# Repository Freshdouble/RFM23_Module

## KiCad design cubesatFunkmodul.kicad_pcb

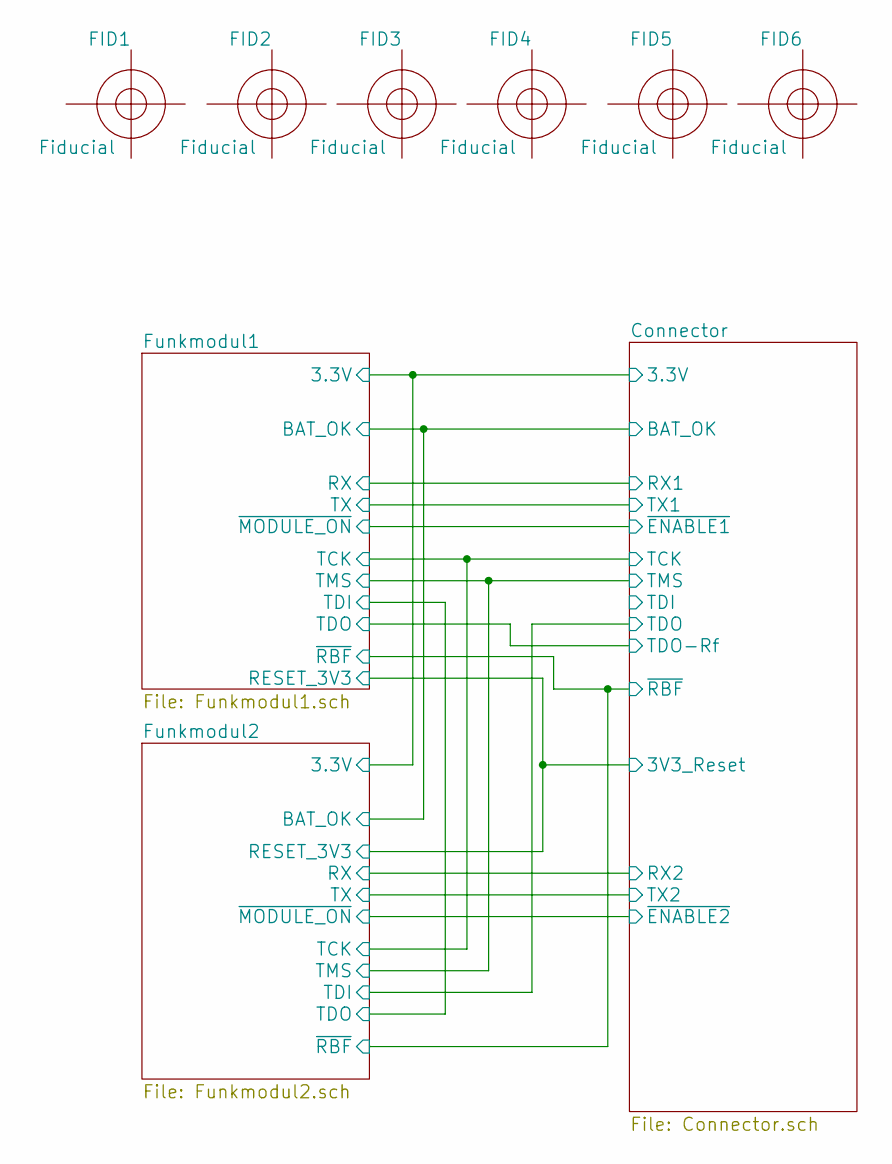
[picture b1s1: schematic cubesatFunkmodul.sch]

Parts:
FID1, FID2, FID3, FID4, FID5, FID6: Fiducial; Fiducial_0.5mm_Dia_1mm_Outer

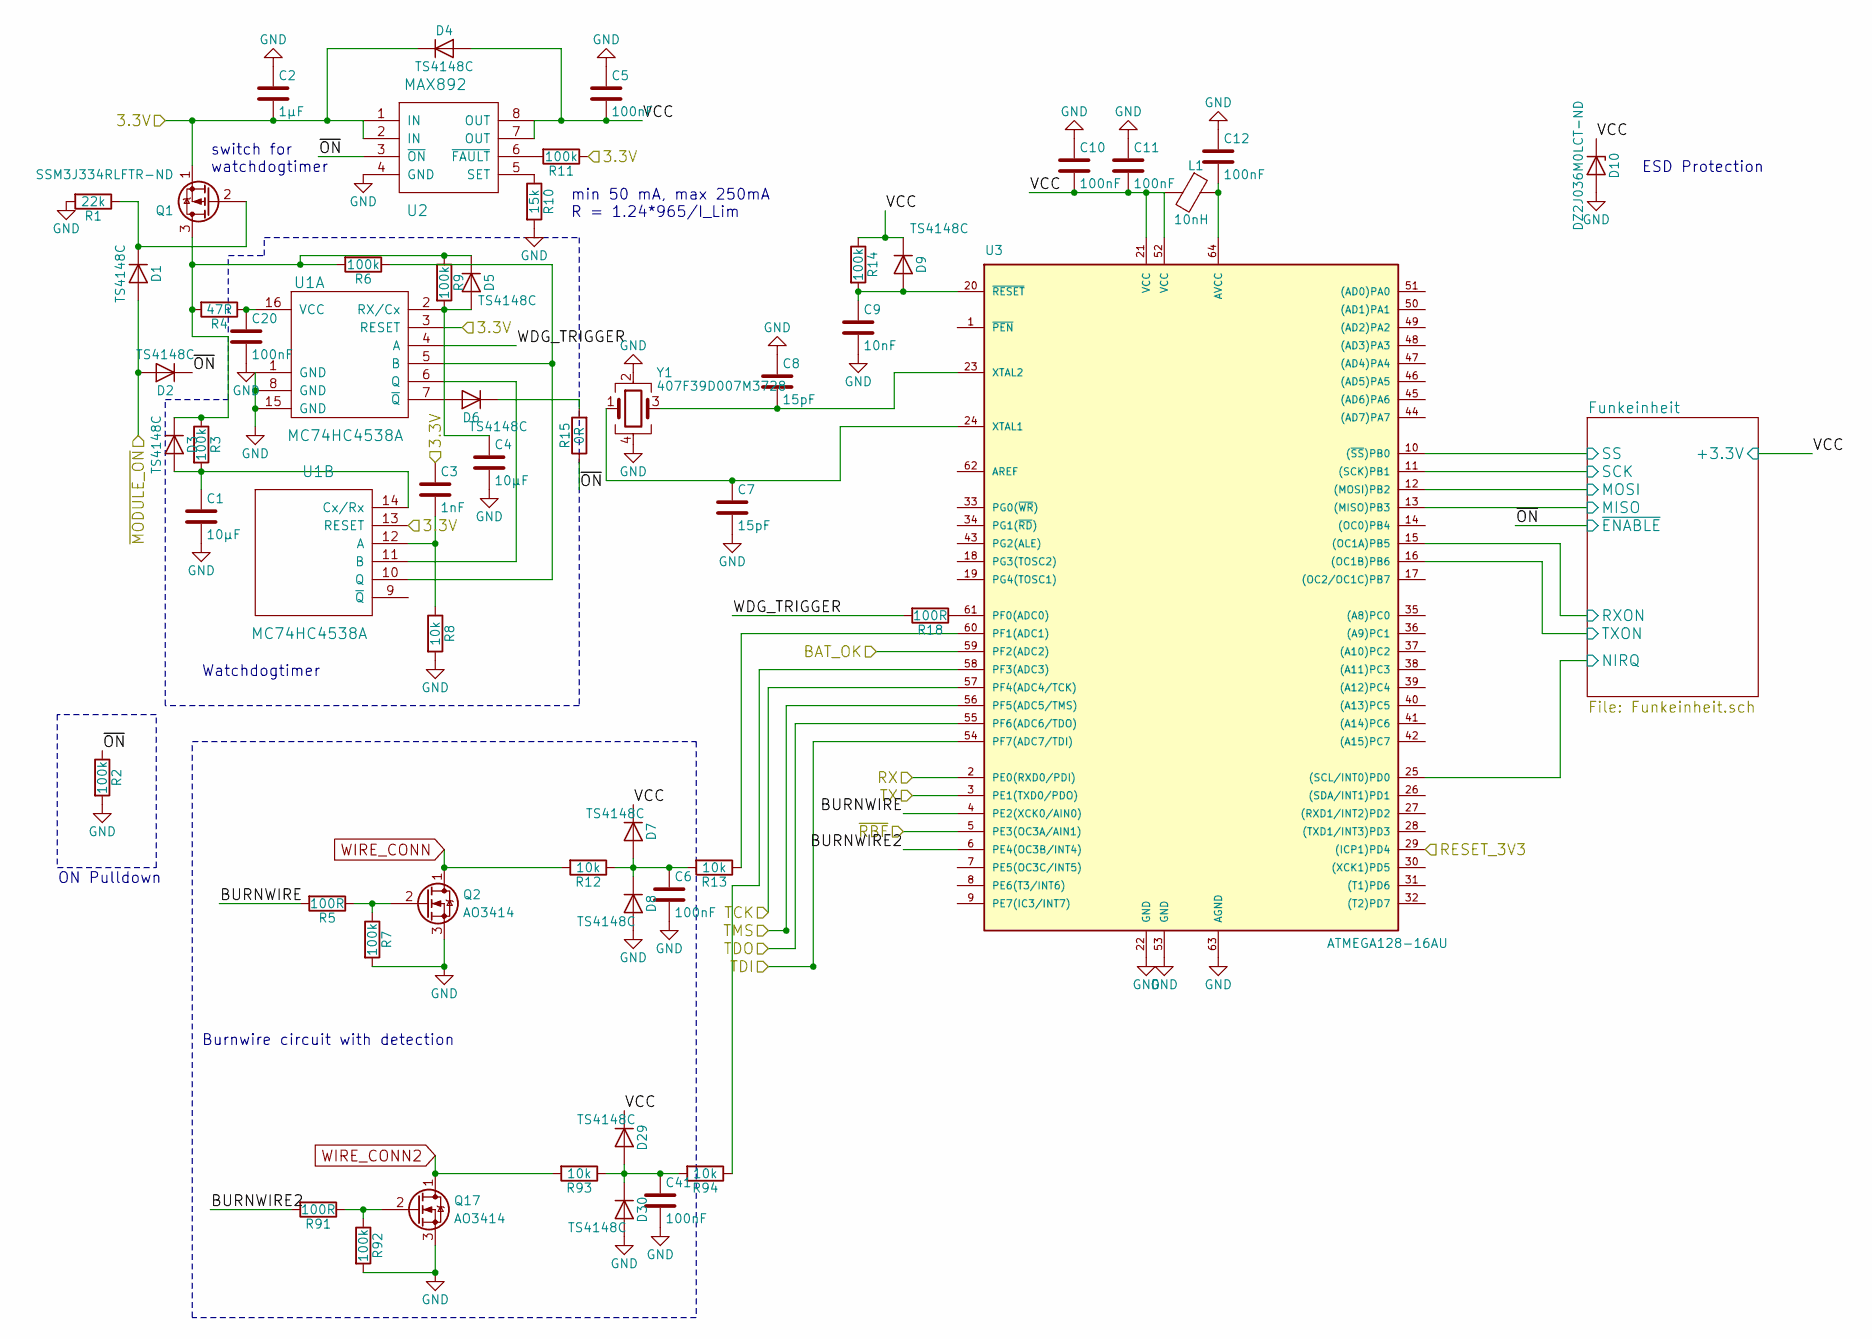
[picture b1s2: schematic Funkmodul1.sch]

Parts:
C1, C4: 10µF; C_1210_HandSoldering
C2: 1µF; C_1210_HandSoldering
C3: 1nF; C_0603_HandSoldering
C5, C6, C10, C11, C12, C20, C41: 100nF; C_0603_HandSoldering
C7, C8: 15pF; C_0603_HandSoldering
C9: 10nF; C_0603_HandSoldering
D1, D2, D3, D4, D5, D6, D7, D8, D9, D29, D30: TS4148C; D_0603
D10: DZ2J036M0LCT-ND; D_SOD-323F
L1: 10nH; L_0603_HandSoldering
Q1: SSM3J334RLFTR-ND; SOT-23
Q2, Q17: AO3414; SOT-23
R1: 22k; R_0603_HandSoldering
R2, R3, R6, R7, R9, R11, R14, R92: 100k; R_0603_HandSoldering
R4: 47R; R_0603_HandSoldering
R5, R18, R91: 100R; R_0603_HandSoldering
R8, R12, R13, R93, R94: 10k; R_0603_HandSoldering
R10: 15k; R_0603_HandSoldering
R15: 0R; R_0805_HandSoldering
U1: MC74HC4538A; SOIC-16_3.9x9.9mm_Pitch1.27mm
U2: MAX892; µMAX-8
U3: ATMEGA128-16AU; TQFP-64_14x14mm_Pitch0.8mm
Y1: 407F39D007M3728; Crystal_SMD_7050-4pin_7.0x5.0mm

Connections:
/Connector/3.3V: C2.2, C3.1, D4.1 (K), Q1.1 (S), R11.1, U1.3 (RESET), U1.13 (RESET), U2.1 (IN), U2.2 (IN); also elsewhere on the board
/Connector/3V3_Reset: U3.29 ((ICP1)PD4); also elsewhere on the board
/Connector/BAT_OK: U3.59 (PF2(ADC2)); also elsewhere on the board
/Connector/TCK: U3.57 (PF4(ADC4/TCK)); also elsewhere on the board
/Connector/TMS: U3.56 (PF5(ADC5/TMS)); also elsewhere on the board
/Connector/~ENABLE1~: D1.2 (A), D2.2 (A); also elsewhere on the board
/Connector/~RBF~: U3.5 (PE3(OC3A/AIN1)); also elsewhere on the board
/Funkmodul1/BURNWIRE: R5.2, U3.4 (PE2(XCK0/AIN0))
/Funkmodul1/BURNWIRE2: R91.2, U3.6 (PE4(OC3B/INT4))
/Funkmodul1/Funkeinheit/MISO: U3.13 ((MISO)PB3); also elsewhere on the board
/Funkmodul1/Funkeinheit/MOSI: U3.12 ((MOSI)PB2); also elsewhere on the board
/Funkmodul1/Funkeinheit/NIRQ: U3.25 ((SCL/INT0)PD0); also elsewhere on the board
/Funkmodul1/Funkeinheit/RXON: U3.15 ((OC1A)PB5); also elsewhere on the board
/Funkmodul1/Funkeinheit/SCK: U3.11 ((SCK)PB1); also elsewhere on the board
/Funkmodul1/Funkeinheit/SS: U3.10 ((~SS~)PB0); also elsewhere on the board
/Funkmodul1/Funkeinheit/TXON: U3.16 ((OC1B)PB6); also elsewhere on the board
/Funkmodul1/RX: U3.2 (PE0(RXD0/PDI)); also elsewhere on the board
/Funkmodul1/TDI: U3.54 (PF7(ADC7/TDI)); also elsewhere on the board
/Funkmodul1/TDO: U3.55 (PF6(ADC6/TDO)); also elsewhere on the board
/Funkmodul1/TX: U3.3 (PE1(TXD0/PDO)); also elsewhere on the board
/Funkmodul1/VCC: C5.2, C10.2, C11.2, D4.2 (A), D7.1 (K), D9.1 (K), D10.1 (K), D29.1 (K), L1.2, R14.1, U2.7 (OUT), U2.8 (OUT), U3.21 (VCC), U3.52 (VCC); also elsewhere on the board
/Funkmodul1/WDG_TRIGGER: R18.2, U1.4 (A)
/Funkmodul1/~ON~: D2.1 (K), R2.1, R15.1, U2.3 (~ON~); also elsewhere on the board
GND: C1.2, C2.1, C4.2, C5.1, C6.2, C7.2, C8.1, C9.2, C10.1, C11.1, C12.1, C20.2, C41.2, D8.2 (A), D10.2 (A), D30.2 (A), Q2.3 (S), Q17.3 (S), R1.2, R2.2, R7.2, R8.2, R10.2, R92.2, U1.1 (GND), U1.8 (GND), U1.15 (GND), U2.4 (GND), U3.22 (GND), U3.53 (GND), U3.63 (AGND), Y1.2, Y1.4; also elsewhere on the board
unnamed: C1.1, D3.2 (A), R3.2, U1.14 (Cx/Rx)
unnamed: C3.2, R8.1, U1.12 (A)
unnamed: C4.1, D5.2 (A), R9.2, U1.2 (RX/Cx)
unnamed: C6.1, D7.2 (A), D8.1 (K), R12.1, R13.2
unnamed: C7.1, U3.24 (XTAL1), Y1.1
unnamed: C8.2, U3.23 (XTAL2), Y1.3
unnamed: C9.1, D9.2 (A), R14.2, U3.20 (~RESET)
unnamed: C12.2, L1.1, U3.64 (AVCC)
unnamed: C20.1, R4.1, U1.16 (VCC)
unnamed: C41.1, D29.2 (A), D30.1 (K), R93.1, R94.2
unnamed: D1.1 (K), Q1.2 (G), R1.1
unnamed: D3.1 (K), D5.1 (K), Q1.3 (D), R3.1, R4.2, R6.2, R9.1
unnamed: D6.1 (K), R15.2
unnamed: D6.2 (A), U1.7 (~Q~)
unnamed: Q2.2 (G), R5.1, R7.1
unnamed: Q17.2 (G), R91.1, R92.1
unnamed: R6.1, U1.5 (B), U1.10 (Q)
unnamed: R10.1, U2.5 (SET)
unnamed: R11.2, U2.6 (~FAULT~)
unnamed: R13.1, U3.60 (PF1(ADC1))
unnamed: R18.1, U3.61 (PF0(ADC0))
unnamed: R94.1, U3.58 (PF3(ADC3))
unnamed: U1.6 (Q), U1.11 (B)
WIRE_CONN: Q2.1 (D), R12.2; also elsewhere on the board
WIRE_CONN2: Q17.1 (D), R93.2; also elsewhere on the board

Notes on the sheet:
min 50 mA, max 250mA R = 1.24*965/I_Lim
Burnwire circuit with detection
Watchdogtimer
switch for watchdogtimer
ON Pulldown
ESD Protection

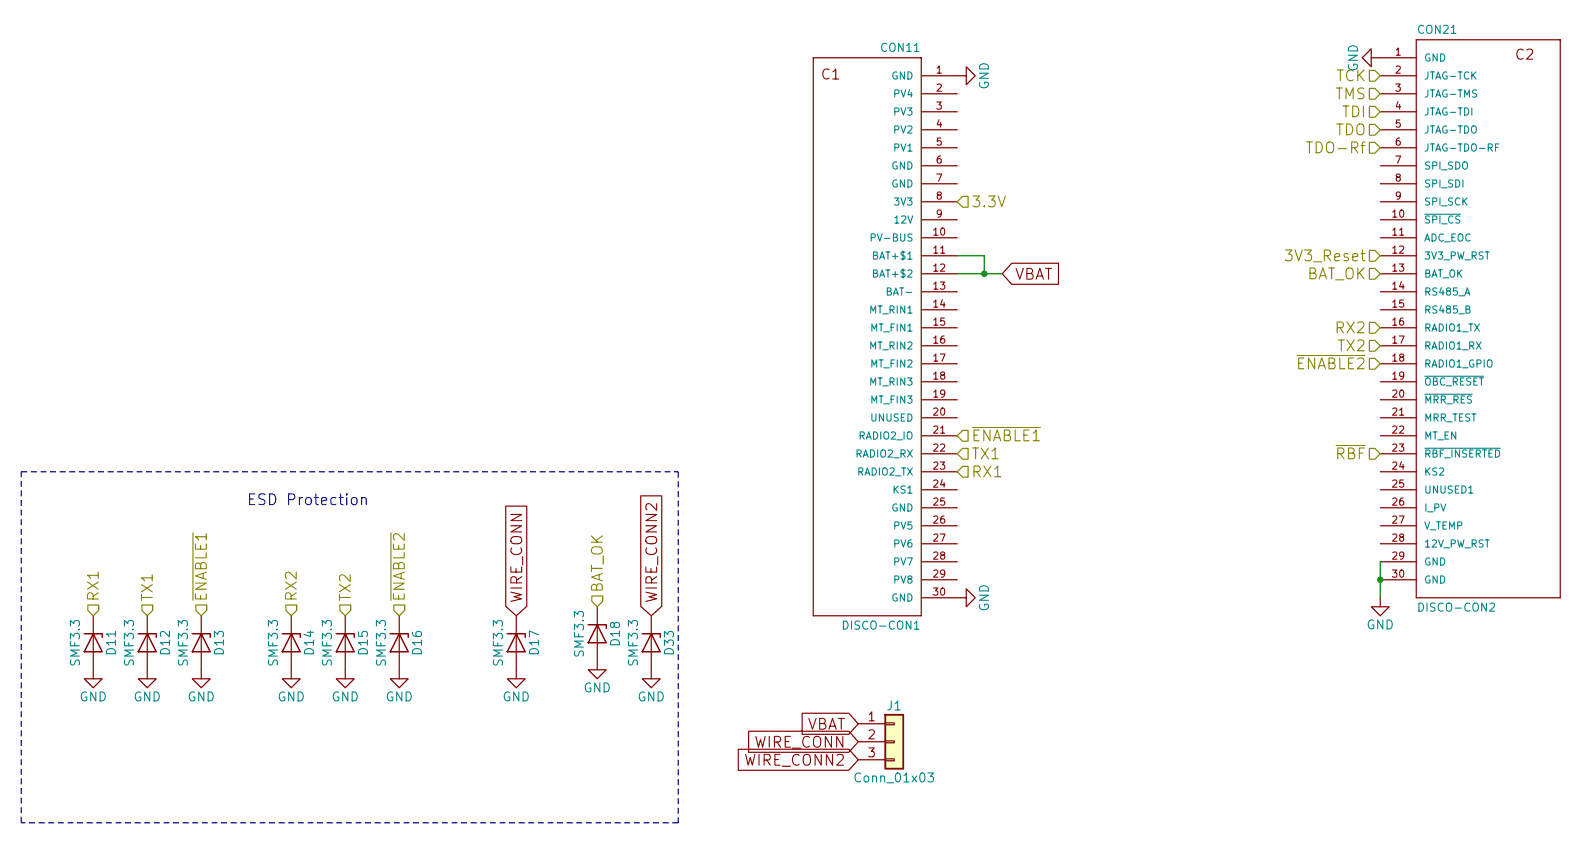
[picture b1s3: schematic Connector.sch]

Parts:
CON11: DISCO-CON1; Cubesatconnector
CON21: DISCO-CON2; Cubesatconnector
D11, D12, D13, D14, D15, D16, D17, D18, D33: SMF3.3; D_SOD-123F
J1: Conn_01x03; Pin_Header_Straight_1x03_Pitch2.54mm

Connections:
/Connector/3.3V: CON11.8 (3V3); also elsewhere on the board
/Connector/3V3_Reset: CON21.12 (3V3_PW_RST); also elsewhere on the board
/Connector/BAT_OK: CON21.13 (BAT_OK), D18.1 (K); also elsewhere on the board
/Connector/TCK: CON21.2 (JTAG-TCK); also elsewhere on the board
/Connector/TDI: CON21.4 (JTAG-TDI)
/Connector/TMS: CON21.3 (JTAG-TMS); also elsewhere on the board
/Connector/~ENABLE1~: CON11.21 (RADIO2_IO), D13.1 (K); also elsewhere on the board
/Connector/~ENABLE2~: CON21.18 (RADIO1_GPIO), D16.1 (K); also elsewhere on the board
/Connector/~RBF~: CON21.23 (~RBF_INSERTED); also elsewhere on the board
/Funkmodul1/RX: CON11.23 (RADIO2_TX), D11.1 (K); also elsewhere on the board
/Funkmodul1/TDO: CON21.6 (JTAG-TDO-RF); also elsewhere on the board
/Funkmodul1/TX: CON11.22 (RADIO2_RX), D12.1 (K); also elsewhere on the board
/Funkmodul2/RX: CON21.16 (RADIO1_TX), D14.1 (K); also elsewhere on the board
/Funkmodul2/TDI: CON21.5 (JTAG-TDO); also elsewhere on the board
/Funkmodul2/TX: CON21.17 (RADIO1_RX), D15.1 (K); also elsewhere on the board
GND: CON11.1 (GND), CON11.30 (GND), CON21.1 (GND), CON21.29 (GND), CON21.30 (GND), D11.2 (A), D12.2 (A), D13.2 (A), D14.2 (A), D15.2 (A), D16.2 (A), D17.2 (A), D18.2 (A), D33.2 (A); also elsewhere on the board
VBAT: CON11.11 (BAT+$1), CON11.12 (BAT+$2), J1.1; also elsewhere on the board
WIRE_CONN: D17.1 (K), J1.2; also elsewhere on the board
WIRE_CONN2: D33.1 (K), J1.3; also elsewhere on the board

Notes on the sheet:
ESD Protection

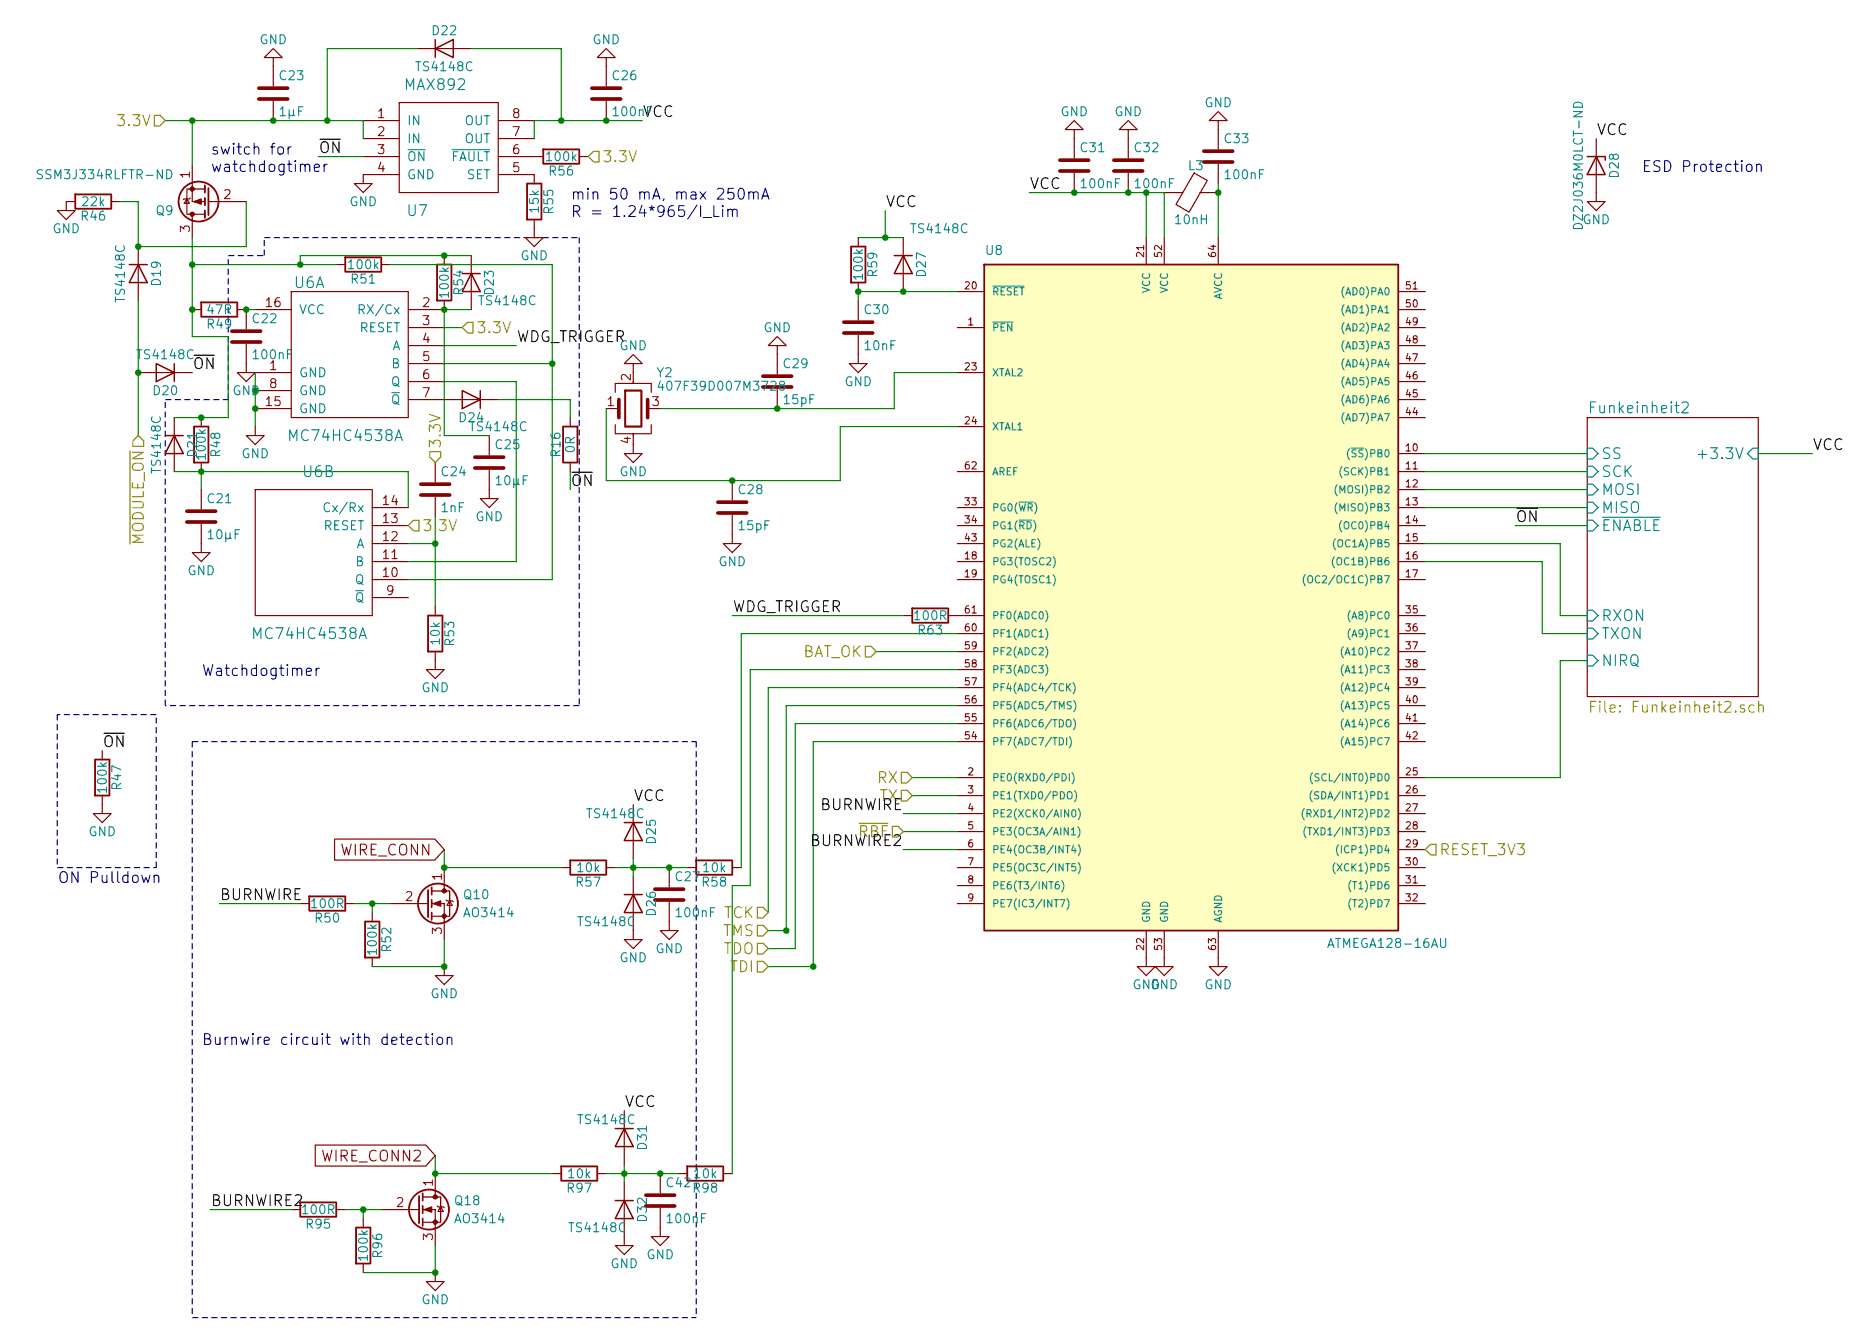
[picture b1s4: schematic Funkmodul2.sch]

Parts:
C21, C25: 10µF; C_1210_HandSoldering
C22, C26, C27, C31, C32, C33, C42: 100nF; C_0603_HandSoldering
C23: 1µF; C_1210_HandSoldering
C24: 1nF; C_0603_HandSoldering
C28, C29: 15pF; C_0603_HandSoldering
C30: 10nF; C_0603_HandSoldering
D19, D20, D21, D22, D23, D24, D25, D26, D27, D31, D32: TS4148C; D_0603
D28: DZ2J036M0LCT-ND; D_SOD-323F
L3: 10nH; L_0603_HandSoldering
Q9: SSM3J334RLFTR-ND; SOT-23
Q10, Q18: AO3414; SOT-23
R16: 0R; R_0805_HandSoldering
R46: 22k; R_0603_HandSoldering
R47, R48, R51, R52, R54, R56, R59, R96: 100k; R_0603_HandSoldering
R49: 47R; R_0603_HandSoldering
R50, R63, R95: 100R; R_0603_HandSoldering
R53, R57, R58, R97, R98: 10k; R_0603_HandSoldering
R55: 15k; R_0603_HandSoldering
U6: MC74HC4538A; SOIC-16_3.9x9.9mm_Pitch1.27mm
U7: MAX892; µMAX-8
U8: ATMEGA128-16AU; TQFP-64_14x14mm_Pitch0.8mm
Y2: 407F39D007M3728; Crystal_SMD_7050-4pin_7.0x5.0mm

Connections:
/Connector/3.3V: C23.2, C24.1, D22.1 (K), Q9.1 (S), R56.1, U6.3 (RESET), U6.13 (RESET), U7.1 (IN), U7.2 (IN); also elsewhere on the board
/Connector/3V3_Reset: U8.29 ((ICP1)PD4); also elsewhere on the board
/Connector/BAT_OK: U8.59 (PF2(ADC2)); also elsewhere on the board
/Connector/TCK: U8.57 (PF4(ADC4/TCK)); also elsewhere on the board
/Connector/TMS: U8.56 (PF5(ADC5/TMS)); also elsewhere on the board
/Connector/~ENABLE2~: D19.2 (A), D20.2 (A); also elsewhere on the board
/Connector/~RBF~: U8.5 (PE3(OC3A/AIN1)); also elsewhere on the board
/Funkmodul1/TDI: U8.55 (PF6(ADC6/TDO)); also elsewhere on the board
/Funkmodul2/BURNWIRE: R50.2, U8.4 (PE2(XCK0/AIN0))
/Funkmodul2/BURNWIRE2: R95.2, U8.6 (PE4(OC3B/INT4))
/Funkmodul2/Funkeinheit2/MISO: U8.13 ((MISO)PB3); also elsewhere on the board
/Funkmodul2/Funkeinheit2/MOSI: U8.12 ((MOSI)PB2); also elsewhere on the board
/Funkmodul2/Funkeinheit2/NIRQ: U8.25 ((SCL/INT0)PD0); also elsewhere on the board
/Funkmodul2/Funkeinheit2/RXON: U8.15 ((OC1A)PB5); also elsewhere on the board
/Funkmodul2/Funkeinheit2/SCK: U8.11 ((SCK)PB1); also elsewhere on the board
/Funkmodul2/Funkeinheit2/SS: U8.10 ((~SS~)PB0); also elsewhere on the board
/Funkmodul2/Funkeinheit2/TXON: U8.16 ((OC1B)PB6); also elsewhere on the board
/Funkmodul2/RX: U8.2 (PE0(RXD0/PDI)); also elsewhere on the board
/Funkmodul2/TDI: U8.54 (PF7(ADC7/TDI)); also elsewhere on the board
/Funkmodul2/TX: U8.3 (PE1(TXD0/PDO)); also elsewhere on the board
/Funkmodul2/VCC: C26.2, C31.2, C32.2, D22.2 (A), D25.1 (K), D27.1 (K), D28.1 (K), D31.1 (K), L3.2, R59.1, U7.7 (OUT), U7.8 (OUT), U8.21 (VCC), U8.52 (VCC); also elsewhere on the board
/Funkmodul2/WDG_TRIGGER: R63.2, U6.4 (A)
/Funkmodul2/~ON~: D20.1 (K), R16.1, R47.1, U7.3 (~ON~); also elsewhere on the board
GND: C21.2, C22.2, C23.1, C25.2, C26.1, C27.2, C28.2, C29.1, C30.2, C31.1, C32.1, C33.1, C42.2, D26.2 (A), D28.2 (A), D32.2 (A), Q10.3 (S), Q18.3 (S), R46.2, R47.2, R52.2, R53.2, R55.2, R96.2, U6.1 (GND), U6.8 (GND), U6.15 (GND), U7.4 (GND), U8.22 (GND), U8.53 (GND), U8.63 (AGND), Y2.2, Y2.4; also elsewhere on the board
unnamed: C21.1, D21.2 (A), R48.2, U6.14 (Cx/Rx)
unnamed: C22.1, R49.1, U6.16 (VCC)
unnamed: C24.2, R53.1, U6.12 (A)
unnamed: C25.1, D23.2 (A), R54.2, U6.2 (RX/Cx)
unnamed: C27.1, D25.2 (A), D26.1 (K), R57.1, R58.2
unnamed: C28.1, U8.24 (XTAL1), Y2.1
unnamed: C29.2, U8.23 (XTAL2), Y2.3
unnamed: C30.1, D27.2 (A), R59.2, U8.20 (~RESET)
unnamed: C33.2, L3.1, U8.64 (AVCC)
unnamed: C42.1, D31.2 (A), D32.1 (K), R97.1, R98.2
unnamed: D19.1 (K), Q9.2 (G), R46.1
unnamed: D21.1 (K), D23.1 (K), Q9.3 (D), R48.1, R49.2, R51.2, R54.1
unnamed: D24.1 (K), R16.2
unnamed: D24.2 (A), U6.7 (~Q~)
unnamed: Q10.2 (G), R50.1, R52.1
unnamed: Q18.2 (G), R95.1, R96.1
unnamed: R51.1, U6.5 (B), U6.10 (Q)
unnamed: R55.1, U7.5 (SET)
unnamed: R56.2, U7.6 (~FAULT~)
unnamed: R58.1, U8.60 (PF1(ADC1))
unnamed: R63.1, U8.61 (PF0(ADC0))
unnamed: R98.1, U8.58 (PF3(ADC3))
unnamed: U6.6 (Q), U6.11 (B)
WIRE_CONN: Q10.1 (D), R57.2; also elsewhere on the board
WIRE_CONN2: Q18.1 (D), R97.2; also elsewhere on the board

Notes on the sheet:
min 50 mA, max 250mA R = 1.24*965/I_Lim
Burnwire circuit with detection
Watchdogtimer
switch for watchdogtimer
ON Pulldown
ESD Protection

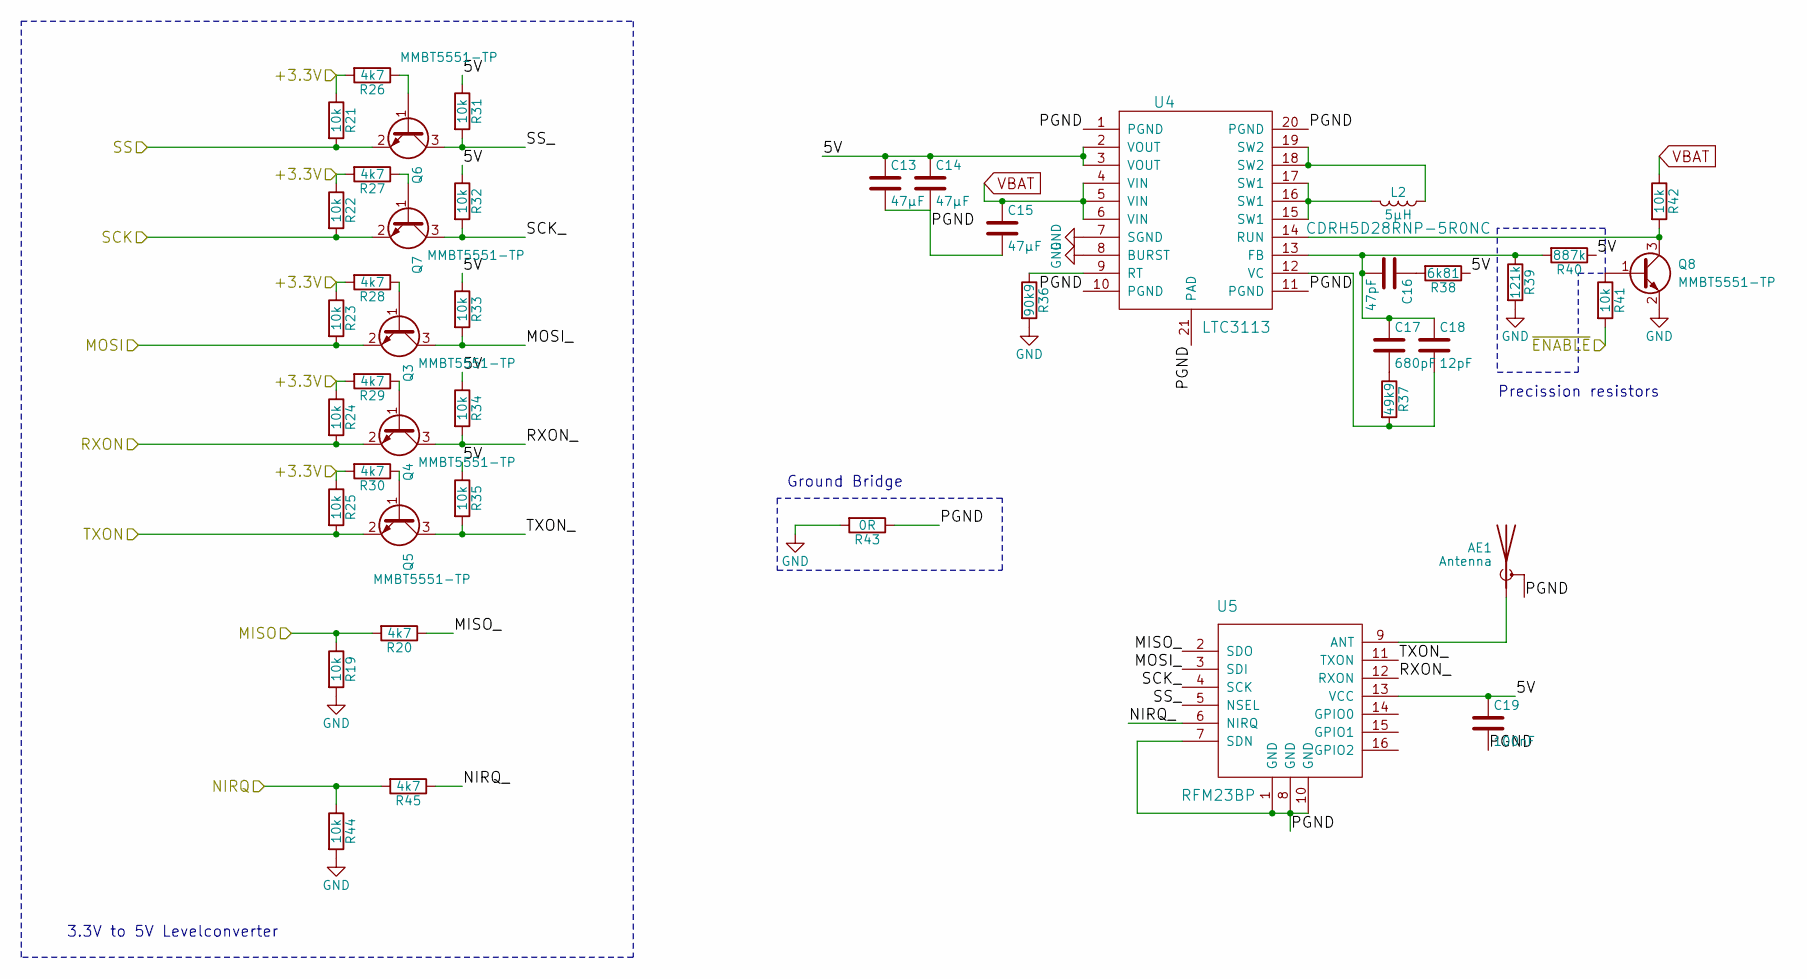
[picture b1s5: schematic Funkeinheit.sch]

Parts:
AE1: Antenna; SMA_THT_Jack_Straight
C13, C14, C15: 47µF; C_1210_HandSoldering
C16: 47pF; C_0603_HandSoldering
C17: 680pF; C_0603_HandSoldering
C18: 12pF; C_0603_HandSoldering
C19: 100nF; C_0603_HandSoldering
L2: 5µH; L_6.3x6.3_H3
Q3, Q4, Q5, Q6, Q7, Q8: MMBT5551-TP; SOT-23
R19, R21, R22, R23, R24, R25, R31, R32, R33, R34, R35, R41, R42, R44: 10k; R_0603_HandSoldering
R20, R26, R27, R28, R29, R30, R45: 4k7; R_0603_HandSoldering
R36: 90k9; R_0603_HandSoldering
R37: 49k9; R_0603_HandSoldering
R38: 6k81; R_0603_HandSoldering
R39: 121k; R_0603_HandSoldering
R40: 887k; R_0603_HandSoldering
R43: 0R; R_0603_HandSoldering
U4: LTC3113; HTSSOP-20-1EP_4.4x6.5mm_Pitch0.65mm_ThermalPad
U5: RFM23BP

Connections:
/Funkmodul1/Funkeinheit/5V: C13.1, C14.1, C19.1, R31.1, R32.1, R33.1, R34.1, R35.1, R38.1, R40.1, U4.2 (VOUT), U4.3 (VOUT), U5.13 (VCC)
/Funkmodul1/Funkeinheit/MISO: R19.1, R20.2; also elsewhere on the board
/Funkmodul1/Funkeinheit/MISO_: R20.1, U5.2 (SDO)
/Funkmodul1/Funkeinheit/MOSI: Q3.2 (E), R23.2; also elsewhere on the board
/Funkmodul1/Funkeinheit/MOSI_: Q3.3 (C), R33.2, U5.3 (SDI)
/Funkmodul1/Funkeinheit/NIRQ: R44.1, R45.2; also elsewhere on the board
/Funkmodul1/Funkeinheit/NIRQ_: R45.1, U5.6 (NIRQ)
/Funkmodul1/Funkeinheit/PGND: AE1.2 (Shield), C13.2, C14.2, C15.2, C19.2, R43.1, U4.1 (PGND), U4.10 (PGND), U4.11 (PGND), U4.20 (PGND), U4.21 (PAD), U5.1 (GND), U5.7 (SDN), U5.8 (GND), U5.10 (GND)
/Funkmodul1/Funkeinheit/RXON: Q4.2 (E), R24.2; also elsewhere on the board
/Funkmodul1/Funkeinheit/RXON_: Q4.3 (C), R34.2, U5.12 (RXON)
/Funkmodul1/Funkeinheit/SCK: Q7.2 (E), R22.2; also elsewhere on the board
/Funkmodul1/Funkeinheit/SCK_: Q7.3 (C), R32.2, U5.4 (SCK)
/Funkmodul1/Funkeinheit/SS: Q6.2 (E), R21.2; also elsewhere on the board
/Funkmodul1/Funkeinheit/SS_: Q6.3 (C), R31.2, U5.5 (NSEL)
/Funkmodul1/Funkeinheit/TXON: Q5.2 (E), R25.2; also elsewhere on the board
/Funkmodul1/Funkeinheit/TXON_: Q5.3 (C), R35.2, U5.11 (TXON)
/Funkmodul1/VCC: R21.1, R22.1, R23.1, R24.1, R25.1, R26.2, R27.2, R28.2, R29.2, R30.2; also elsewhere on the board
/Funkmodul1/~ON~: R41.2; also elsewhere on the board
GND: Q8.2 (E), R19.2, R36.2, R39.2, R43.2, R44.2, U4.7 (SGND), U4.8 (BURST); also elsewhere on the board
unnamed: AE1.1 (A), U5.9 (ANT)
unnamed: C16.1, R38.2
unnamed: C16.2, C17.1, C18.1, R39.1, R40.2, U4.13 (FB)
unnamed: C17.2, R37.1
unnamed: C18.2, R37.2, U4.12 (VC)
unnamed: L2.1, U4.18 (SW2), U4.19 (SW2)
unnamed: L2.2, U4.15 (SW1), U4.16 (SW1), U4.17 (SW1)
unnamed: Q3.1 (B), R28.1
unnamed: Q4.1 (B), R29.1
unnamed: Q5.1 (B), R30.1
unnamed: Q6.1 (B), R26.1
unnamed: Q7.1 (B), R27.1
unnamed: Q8.1 (B), R41.1
unnamed: Q8.3 (C), R42.2, U4.14 (RUN)
unnamed: R36.1, U4.9 (RT)
VBAT: C15.1, R42.1, U4.4 (VIN), U4.5 (VIN), U4.6 (VIN); also elsewhere on the board

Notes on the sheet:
Ground Bridge
Precission resistors
3.3V to 5V Levelconverter

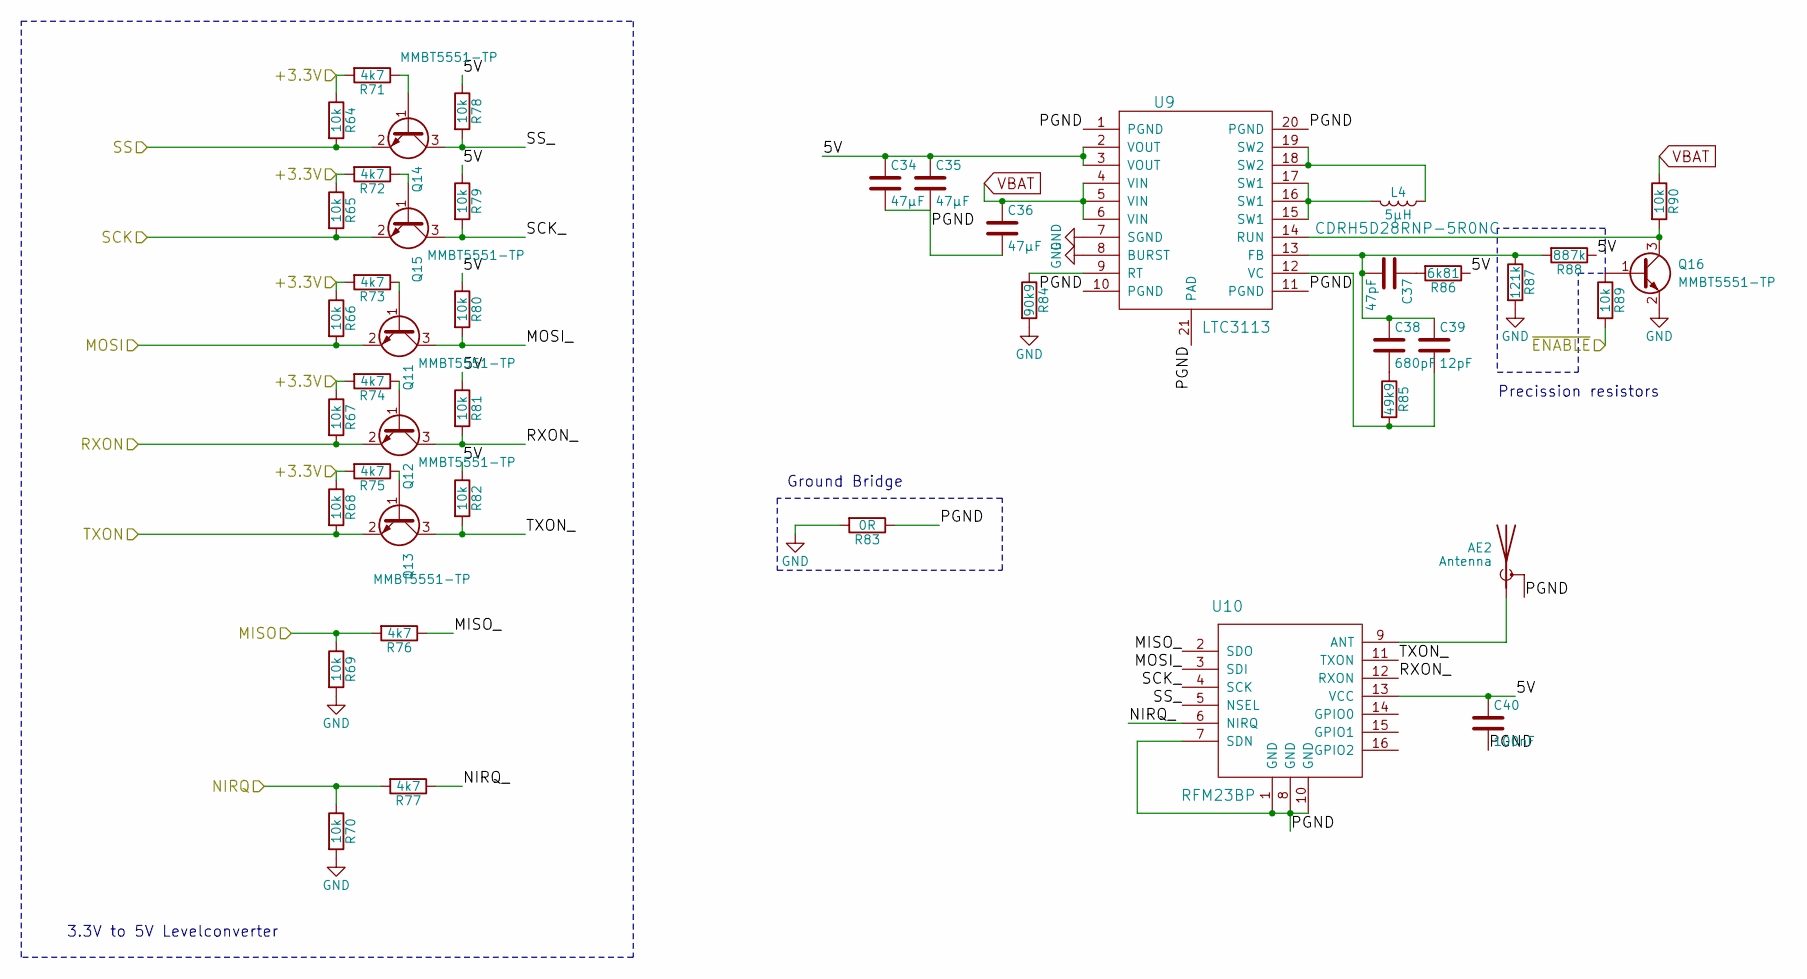
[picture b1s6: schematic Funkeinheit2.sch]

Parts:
AE2: Antenna; SMA_THT_Jack_Straight
C34, C35, C36: 47µF; C_1210_HandSoldering
C37: 47pF; C_0603_HandSoldering
C38: 680pF; C_0603_HandSoldering
C39: 12pF; C_0603_HandSoldering
C40: 100nF; C_0603_HandSoldering
L4: 5µH; L_6.3x6.3_H3
Q11, Q12, Q13, Q14, Q15, Q16: MMBT5551-TP; SOT-23
R64, R65, R66, R67, R68, R69, R70, R78, R79, R80, R81, R82, R89, R90: 10k; R_0603_HandSoldering
R71, R72, R73, R74, R75, R76, R77: 4k7; R_0603_HandSoldering
R83: 0R; R_0603_HandSoldering
R84: 90k9; R_0603_HandSoldering
R85: 49k9; R_0603_HandSoldering
R86: 6k81; R_0603_HandSoldering
R87: 121k; R_0603_HandSoldering
R88: 887k; R_0603_HandSoldering
U9: LTC3113; HTSSOP-20-1EP_4.4x6.5mm_Pitch0.65mm_ThermalPad
U10: RFM23BP

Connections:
/Funkmodul2/Funkeinheit2/5V: C34.1, C35.1, C40.1, R78.1, R79.1, R80.1, R81.1, R82.1, R86.1, R88.1, U9.2 (VOUT), U9.3 (VOUT), U10.13 (VCC)
/Funkmodul2/Funkeinheit2/MISO: R69.1, R76.2; also elsewhere on the board
/Funkmodul2/Funkeinheit2/MISO_: R76.1, U10.2 (SDO)
/Funkmodul2/Funkeinheit2/MOSI: Q11.2 (E), R66.2; also elsewhere on the board
/Funkmodul2/Funkeinheit2/MOSI_: Q11.3 (C), R80.2, U10.3 (SDI)
/Funkmodul2/Funkeinheit2/NIRQ: R70.1, R77.2; also elsewhere on the board
/Funkmodul2/Funkeinheit2/NIRQ_: R77.1, U10.6 (NIRQ)
/Funkmodul2/Funkeinheit2/PGND: AE2.2 (Shield), C34.2, C35.2, C36.2, C40.2, R83.1, U9.1 (PGND), U9.10 (PGND), U9.11 (PGND), U9.20 (PGND), U9.21 (PAD), U10.1 (GND), U10.7 (SDN), U10.8 (GND), U10.10 (GND)
/Funkmodul2/Funkeinheit2/RXON: Q12.2 (E), R67.2; also elsewhere on the board
/Funkmodul2/Funkeinheit2/RXON_: Q12.3 (C), R81.2, U10.12 (RXON)
/Funkmodul2/Funkeinheit2/SCK: Q15.2 (E), R65.2; also elsewhere on the board
/Funkmodul2/Funkeinheit2/SCK_: Q15.3 (C), R79.2, U10.4 (SCK)
/Funkmodul2/Funkeinheit2/SS: Q14.2 (E), R64.2; also elsewhere on the board
/Funkmodul2/Funkeinheit2/SS_: Q14.3 (C), R78.2, U10.5 (NSEL)
/Funkmodul2/Funkeinheit2/TXON: Q13.2 (E), R68.2; also elsewhere on the board
/Funkmodul2/Funkeinheit2/TXON_: Q13.3 (C), R82.2, U10.11 (TXON)
/Funkmodul2/VCC: R64.1, R65.1, R66.1, R67.1, R68.1, R71.2, R72.2, R73.2, R74.2, R75.2; also elsewhere on the board
/Funkmodul2/~ON~: R89.2; also elsewhere on the board
GND: Q16.2 (E), R69.2, R70.2, R83.2, R84.2, R87.2, U9.7 (SGND), U9.8 (BURST); also elsewhere on the board
unnamed: AE2.1 (A), U10.9 (ANT)
unnamed: C37.1, R86.2
unnamed: C37.2, C38.1, C39.1, R87.1, R88.2, U9.13 (FB)
unnamed: C38.2, R85.1
unnamed: C39.2, R85.2, U9.12 (VC)
unnamed: L4.1, U9.18 (SW2), U9.19 (SW2)
unnamed: L4.2, U9.15 (SW1), U9.16 (SW1), U9.17 (SW1)
unnamed: Q11.1 (B), R73.1
unnamed: Q12.1 (B), R74.1
unnamed: Q13.1 (B), R75.1
unnamed: Q14.1 (B), R71.1
unnamed: Q15.1 (B), R72.1
unnamed: Q16.1 (B), R89.1
unnamed: Q16.3 (C), R90.2, U9.14 (RUN)
unnamed: R84.1, U9.9 (RT)
VBAT: C36.1, R90.1, U9.4 (VIN), U9.5 (VIN), U9.6 (VIN); also elsewhere on the board

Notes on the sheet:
Ground Bridge
Precission resistors
3.3V to 5V Levelconverter
